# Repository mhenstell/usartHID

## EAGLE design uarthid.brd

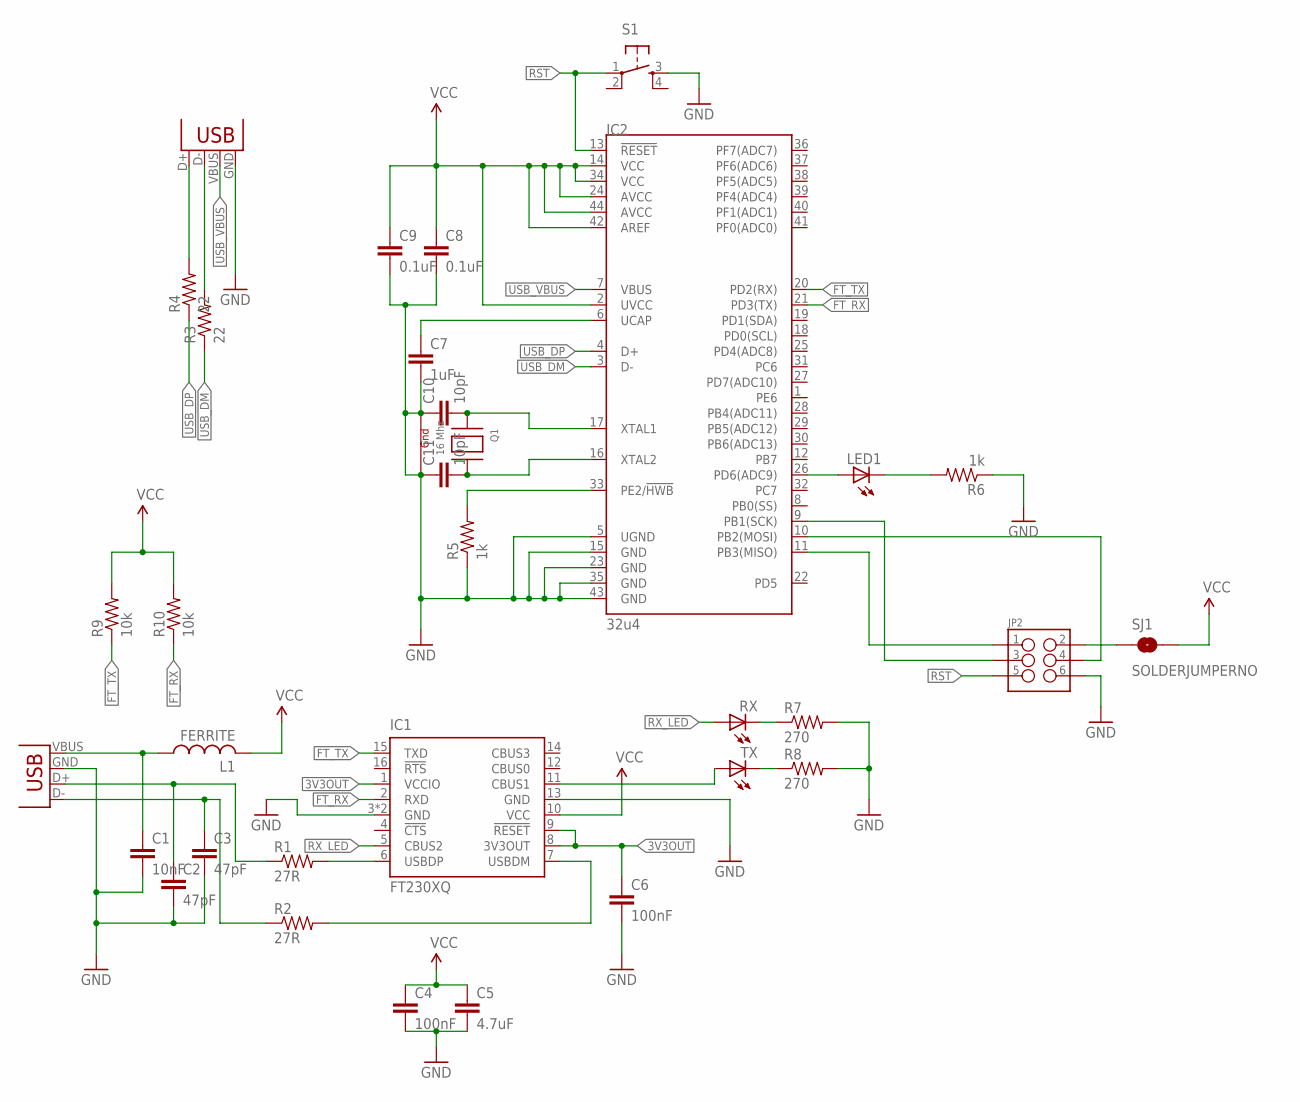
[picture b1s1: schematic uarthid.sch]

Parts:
C1: 10nF; 0805
C2, C3: 47pF; 0805
C4, C6: 100nF; 0805
C5: 4.7uF; 0805
C7: 1uF; 0805
C8, C9: 0.1uF; 0805
C10, C11: 10pF; 0805
IC1: FT230XQ; QFN16; PARTNO FT230XQ-T
IC2: 32u4; SPARKFUN-DIGITALIC_QFN-44; PARTNO ATMEGA32U4RC-MU
JP1: USB-A-H; PARTNO 1002-015-01001
JP2: M03X22X3_SILK_SM; 2X3
JP3: USBSMD; USB-MINIB; PARTNO 690-005-299-043
L1: FERRITE; 0805; PARTNO CIM21J601NE
LED1: LEDCHIPLED_0805; CHIPLED_0805
Q1: 16 Mhz; NX3225; PARTNO TSX-3225 16.0000MF18X-AC3
R1, R2: 27R; 0805
R3, R4: 22; 0805
R5, R6: 1k; 0805
R7, R8: 270; 0805
R9, R10: 10k; 0805
RX: LEDCHIPLED_0805; CHIPLED_0805
S1: TAC_SWITCHSMD; TACTILE_SWITCH_SMD
SJ1: SOLDERJUMPERNO; SJ_2S-NO
TX: LEDCHIPLED_0805; CHIPLED_0805

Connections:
3V3OUT: C6.1, IC1.1 (VCCIO), IC1.8 (3V3OUT), IC1.9 (!RESET)
FT_RX: IC1.2 (RXD), IC2.21 (PD3(TX)), R10.1
FT_TX: IC1.15 (TXD), IC2.20 (PD2(RX)), R9.1
GND: C1.2, C2.2, C3.2, C4.2, C5.2, C6.2, C7.2, C8.2, C9.2, C10.1, C11.1, IC1.3 (GND), IC1.13 (GND), IC1.TAB (GND), IC2.5 (UGND), IC2.15 (GND), IC2.23 (GND), IC2.35 (GND), IC2.43 (GND), JP1.GND (VBUS), JP2.6, JP3.GND, Q1.2 (G2), Q1.4 (G1), R5.1, R6.1, R7.2, R8.2, S1.3
unnamed: C2.1, JP1.D+ (D-), R1.1
unnamed: IC1.6 (USBDP), R1.2
unnamed: C3.1, JP1.D- (D+), R2.1
unnamed: IC1.7 (USBDM), R2.2
unnamed: C1.1, JP1.VBUS (GND), L1.1
unnamed: C10.2, IC2.17 (XTAL1), Q1.1 (X1)
unnamed: C11.2, IC2.16 (XTAL2), Q1.3 (X2)
unnamed: JP3.D-, R3.2
unnamed: JP3.D+, R4.2
unnamed: JP2.2, SJ1.1
unnamed: C7.1, IC2.6 (UCAP)
unnamed: IC2.11 (PB3(MISO)), JP2.1
unnamed: IC2.9 (PB1(SCK)), JP2.3
unnamed: IC2.10 (PB2(MOSI)), JP2.4
unnamed: IC2.33 (PE2/!HWB), R5.2
unnamed: IC2.26 (PD6(ADC9)), LED1.A
unnamed: LED1.C, R6.2
unnamed: IC1.11 (CBUS1), TX.A
unnamed: R7.1, RX.C
unnamed: R8.1, TX.C
RST: IC2.13 (!RESET), JP2.5, S1.1
RX_LED: IC1.5 (CBUS2), RX.A
USB_DM: IC2.3 (D-), R3.1
USB_DP: IC2.4 (D+), R4.1
USB_VBUS: IC2.7 (VBUS), JP3.VBUS
VCC: C4.1, C5.1, C8.1, C9.1, IC1.10 (VCC), IC2.2 (UVCC), IC2.14 (VCC), IC2.24 (AVCC), IC2.34 (VCC), IC2.42 (AREF), IC2.44 (AVCC), L1.2, R9.2, R10.2, SJ1.2

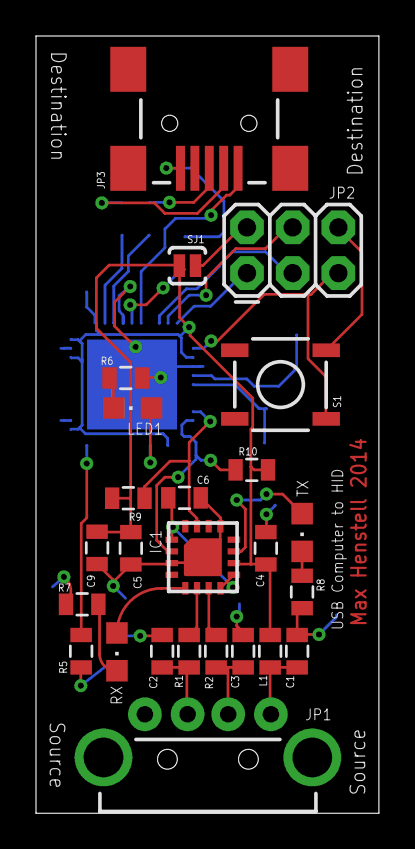
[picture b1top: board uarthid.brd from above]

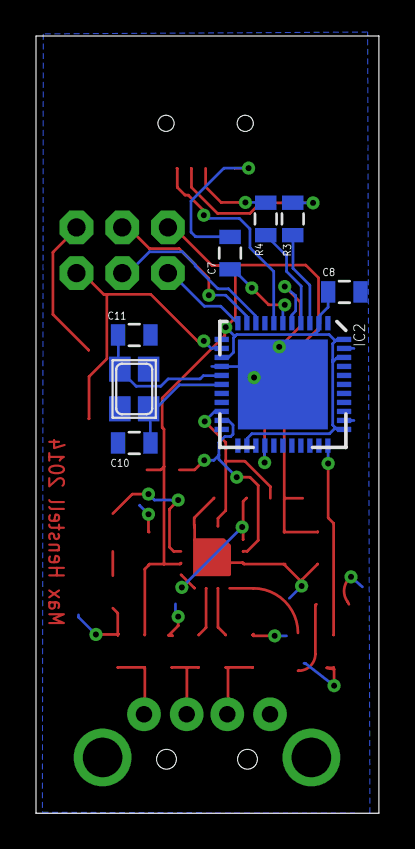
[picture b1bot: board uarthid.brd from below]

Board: 2 copper layers, 19.1 x 43.2 mm, 33 parts (8 on the bottom side), 30 nets.

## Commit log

2014-01-14 init
2014-01-20 routed and bom'd

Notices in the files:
parts and their libraries:
SparkFun-Connectors: Licensing: CC v3.0 Share-Alike You are welcome to use this library for commercial purposes.
